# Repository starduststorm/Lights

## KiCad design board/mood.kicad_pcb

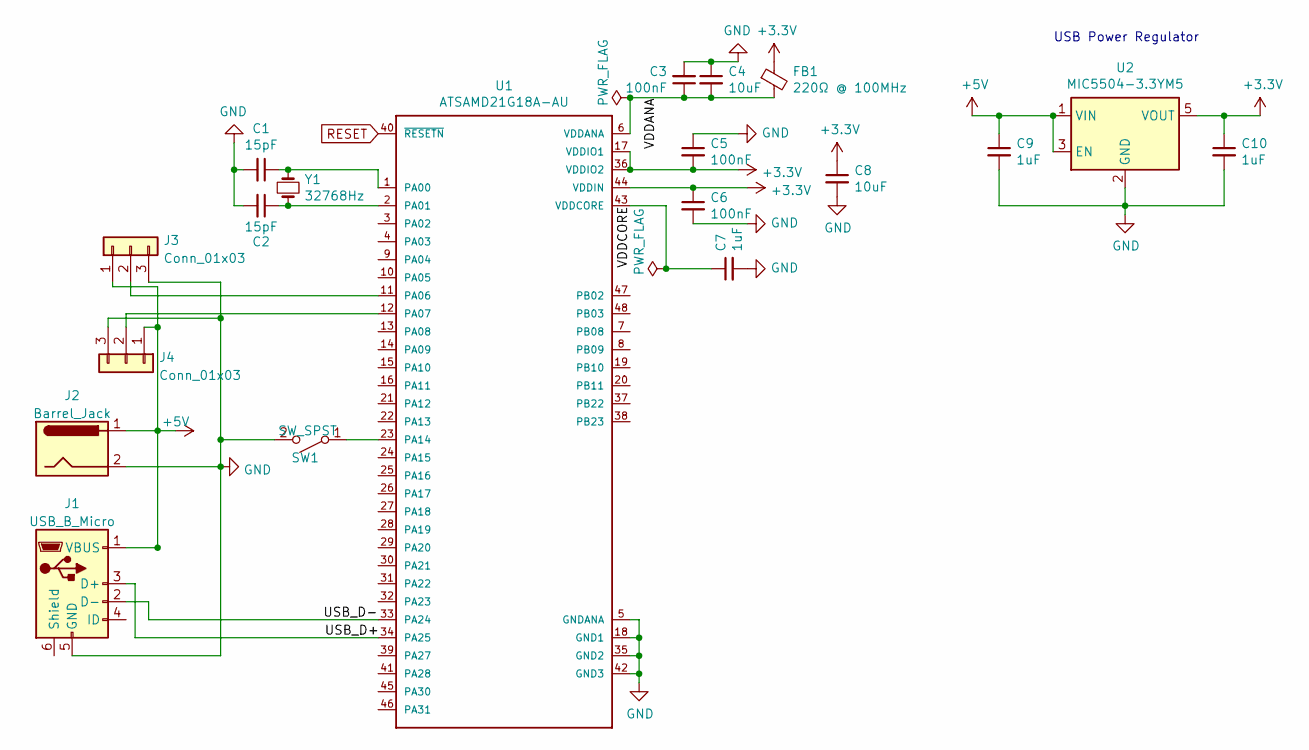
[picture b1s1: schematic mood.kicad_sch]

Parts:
C1, C2: 15pF; C_0402_1005Metric
C3, C5, C6: 100nF; C_0402_1005Metric
C4, C8: 10uF; C_0402_1005Metric
C7, C9, C10: 1uF; C_0603_1608Metric
FB1: 220Ω @ 100MHz; L_0603_1608Metric
J1: USB_B_Micro; USB_Micro-B_GCT_USB3076-30-A
J2: Barrel_Jack; CUI_PJ-063AH
J3, J4: Conn_01x03; PinHeader_1x03_P2.54mm_Horizontal
SW1: SW_SPST; CS1204AF160
U1: ATSAMD21G18A-AU
U2: MIC5504-3.3YM5; SOT-23-5
Y1: 32768Hz; Crystal_SMD_3215-2Pin_3.2x1.5mm

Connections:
+3V3: C5.2, C6.1, C8.1, C10.1, FB1.1, U1.17 (VDDIO1), U1.36 (VDDIO2), U1.44 (VDDIN), U2.5 (VOUT)
+5V: C9.1, J1.1 (VBUS), J2.1, J3.1, J4.1, U2.1 (VIN), U2.3 (EN)
/USB_D+: J1.3 (D+), U1.34 (PA25)
/USB_D-: J1.2 (D-), U1.33 (PA24)
/VDDANA: C3.1, C4.2, FB1.2, U1.6 (VDDANA)
/VDDCORE: C7.1, U1.43 (VDDCORE)
GND: C1.2, C2.2, C3.2, C4.1, C5.1, C6.2, C7.2, C8.2, C9.2, C10.2, J1.5 (GND), J2.2, J3.3, J4.3, SW1.2 (B), U1.5 (GNDANA), U1.18 (GND1), U1.35 (GND2), U1.42 (GND3), U2.2 (GND)
unnamed: C1.1, U1.1 (PA00), Y1.1
unnamed: C2.1, U1.2 (PA01), Y1.2
unnamed: J3.2, U1.11 (PA06)
unnamed: J4.2, U1.12 (PA07)
unnamed: SW1.1 (A), U1.23 (PA14)
RESET: U1.40 (~RESETN)

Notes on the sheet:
USB Power Regulator

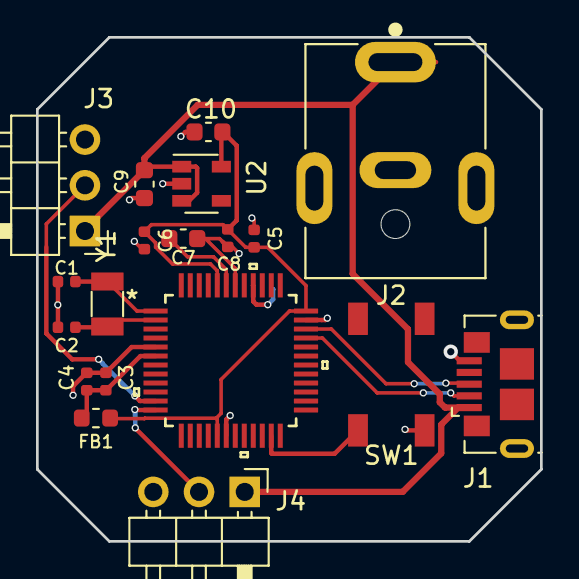
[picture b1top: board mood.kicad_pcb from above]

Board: 2 copper layers, 28.0 x 28.0 mm, 19 parts (0 on the bottom side), 12 nets.

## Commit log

2014-06-01 Initial commit of lighting scene controller * Support for creating and transitioning between several lighting modes * Easy per-light fading loops to make it easy to never abruptly change the lighting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
2014-06-01 * Added "fire" mode * Periodic mode switching * Debug logging
2014-06-03 Added Lightning Bugs mode
2014-06-03 Use a Light* array instead of a Light array for code size and cleanliness
2014-06-26 Blue fire mode, simple waves mode, couple junk modes; appearance tweaks
2014-07-04 Add delay ranges for modes to avoid playing modes at the wrong speeds
2014-07-04 Remove BMModeTest
2014-07-10 * Add new mode "Interfering Waves" * Add "automatic colors" for modes to use to easily get slowly changing colors * Easy hook to test a mode
2014-07-30 * Added some memory debugging code, since I hit the ram limit on the Uno * Added non-working BoomResponder mode * Fix delay ranges on new, unspecified modes * Fix transitioning into Follow
2014-07-30 * Added perf measurement code, since even the mega is having trouble driving a couple modes on 150 lights * Removed some unnecessary float divisions in interpolation, doesn't help much * Added potent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
2014-07-30 Put in a light switch
2014-07-30 Switch to integer math for color interpolation, gaining 1 fps on interfering waves :(
2014-07-30 * Replace usages of random() with a custom rand that is much faster, solving the perf problems with Fire (but not interfering waves) * Use integer math for automatic colors for a tiny perf win
2014-08-01 * Randomize direction when starting a new mode * Add two presets to the wave pattern, since one big wave looks really nice * Use automatic colors for wave mode * Disable interfering waves and make ot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
2014-08-01 Tuning the experience: * Show the lightning bugs mode iff the speed dial is turned to slowest. "Night Mode" * Reduce number of bugs. of lightning. * Fix wave actually using all lights * Fix 90-second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
2014-08-07 Split the two Waves mode variants into two different modes (like fire and blue fire)
2014-08-16 * Change pattern direction when moving to each next light instead of swapping strand update order. The old way caused the strand to flip jarringly when changing to the opposite direction. * Use trans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
2014-08-17 * Add logf * Save a few hundred float multiplies per frame in transitionTick, makes fire smooth again on 200 lights * Fix curved transition progress and wave patterns * Fix an issue with new directio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
2014-08-18 Added a brightness dial
2014-08-21 Fix randomMode to not hang when there are no modes matching the current frameDuration; frame duration tweaks
2014-08-21 Very rough sound response; flashes brighter on sound, doesn't look very good Idea for having colors rotate when a loud enough sound is registered, but would be difficult to make this work for lights 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
2014-08-21 Fix off switch. Had epiphany that lights were turning back on after a 90-second mode change picked the follow mode, which changes colors in setMode.
2015-04-30 * Due support. Kinda. Still too crashy to use. * Fix non-use of developer board * Leaving in logging and crap for tracking down Due crashers, memory smasher, maybe alignment related * Temporary patte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
2015-05-06 Split project into a bunch of headers
2015-05-06 Remove "BM" prefix because it's silly
2015-05-06 Due is now working! Tracked down issues: * Overflowing kModeRanges since it was sized for ModeCount, then delay ranges were set for modes that were "disabled" by being > ModeCount * free()ing uninita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
    Interfering waves is beautiful on 100 lights but needs more variation in where the waves overlap
2015-05-06 Tweaks to automatic color transition rates and perturbation for interfering waves so that they aren't standing waves I should go to bed
2015-05-27 Fix some interfering waves bugs, possibly improve performance, add a transition fade for moving to interfering waves
2015-06-02 Add a ROYGBIV color follow. Really nice looking.
2015-06-10 First pass on a new mode "Accumulator" which drops splotches of color randomly around, then blurs and blends them out
2015-07-03 * New implementation of interfering waves that's way faster, but doesn't quite look right yet and has a bad transition. * Fix random seed at launch
2015-07-08 make interfering waves almost-but-not-exactly color correct. runs smooth on 300 lights.
2015-08-24 Tweaks: lengthen scene and make interfering wave move faster
2015-11-03 Fix dials that seem to have flaky hardware now; start working on mega support for WS2811
2015-11-14 Add support for WS2811 via some assembly I found; factor out into a couple more files
2015-12-01 Factor out some files into header and cpp; futile perf improvements for mega; tweaks for christmas gift
2015-12-05 Add Twinkle mode
2015-12-05 * Fix issue where modes outside delay range weren't picked even though no dev board is used * Don't sometimes turn off all lights in Twinkle * Don't fade through White in Parity * And a Christmas Eas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
2015-12-12 Fix asm instruction timing: sbiw takes 2 cycles, dec took only 1
2015-12-19 Fix a bug where Twinkle might go all dark; slow down twinkle a little; disable Parity since it flickers on the WS2811 lights and is also a bit boring
2017-03-10 Add support for Teensy, just using FastLED; fix build warnings from new arduino IDE; ws2811 assembly is broken now; also add crappy-looking pink fire mode
2017-05-12 * Factor "automatic colors" out of scene * Upgrade various rainbows into Palettes * Slight tweaks to modes
2017-05-16 Remove _followLeader, make _smoothLeader into follow leader
2017-05-16 * Complete rework of animation timing to be based on actual timing instead of selective frame limiters * Remove Follow cause it's boring
2017-05-28 everything's fucked up
2017-08-15 Starting playa prep
2017-08-15 Fixed accumulator, partly fixed lightning bugs. Some patterns don't deal well with global speed adjustments, but overall the new timing is working properly.
2017-08-24 Fix an issue where a strand would be a mix of white and random if it was unplugged and replugged while dev board switch was off
2019-01-14 enhancements for teensy, fire
2019-01-14 Fix parity timing broken by dea97eab
2019-01-14 Fix waves that was broken by an old left-over tweak rolled into af50e7; combine OneBigWave into Waves and make it just large waves that work on various numbers of lights
2019-05-16 tweaks for updating software from xmas megas; compiling on laptop
2019-05-17 fixed lightning bugs timing by just guessing at what looks good; doesn't really match old timing pre-timing-refactor
2019-05-17 Fix Accumulator to look less like it's on a clock
2019-05-17 again tweak lightning bugs to match measured former timing; simplify/improve density wave
2019-05-21 fix transition into lightning bugs
2019-10-11 TCL tweaks, comments
2020-01-15 Fix a bug in InterferringWaves where automaticColorsCount was always 20, would crash at high pixel counts; fix some build warnings
2020-03-27 Moving development environment from Arduino.app to PlatformIO
2020-03-27 Add support for a second strand wired in parallel; convert some floating-point operations into integer math to markedly improve framerate, esp. with 200+ pixels
2020-03-27 palettize ModeWaves; some slight cleanup & modernization
2020-03-27 palettize ModeAccumulator; fix a confusing argument name
2020-03-28 fix single strands
2020-03-28 palettize & rework Parity; fix RNG; fix palette tick on patterns that don't call getPalette on every frame; modernize logging utils
2020-03-31 polish tweaks to ModeParity, Rainbow, and InterferringWaves
2020-03-31 fix unsigned/signed build warning, but there are likely signedness issues throughout this code
2020-04-13 give paletterotation an option to disinclude palettes with sudden color shifts
2020-04-13 split deployment targets using platform.ini; re-add mega and make necessary fixes; move some config flags e.g. LED_COUNT and DOUBLE_STARND to platform.ini
2020-04-14 Work around a memory-related logging crash on mega; Remove "Sound" processing which never worked; isolated some Developer Board features to dev board flags; continue porting various features to integ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
2020-05-02 memory optimizations needed for mega compatibility: only ever pass CRGBPalette256 around by reference/ptr; remove Color filler, replace with cache record; compile out speed ranges by DEVELOPER_BOARD;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
2020-05-02 correct pin for double-strand
2020-05-03 crib frame limiter from belt code (120fps for now) because the performance on teensy 3.1 is now so fast (Accum was at ~260fps) that it's overloading the leds!
2020-09-21 tweak for FastLED compatibility
2021-10-26 add arduino due environment to build for the original Due this project was first written for
2022-12-15 functional WIP for running on samd21
2022-12-15 first pass on a PCB containing minimal circuitry for driving 2 strands of lights on samd21; needs SWD pins
2023-02-15 samd21 software support; add a config for seeed_xiao
2023-10-04 add seeed_xiao_double

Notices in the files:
parts and their libraries:
Copyright 2016 Accelerated Designs. All rights reserved.
